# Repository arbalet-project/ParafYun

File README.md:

# Paraf Project

**Paraf** is an opensource digital water curtain.

## Paraf Yún

Paraf Yún is the first version, whose conception started in October, 2018.
Yún's hardware and software resources are designed by and for University students.
Have a look to the [students' logbook](http://talk.arbalet-project.org/t/paraf-yun-en/126) ([lire en français](http://talk.arbalet-project.org/t/paraf-yun-fr/129/)).

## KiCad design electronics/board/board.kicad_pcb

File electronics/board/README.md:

# BOM

Model / Package
IRF7404 / SO-8
ST485 / SO-8
ULN2803A / DW R-PDSO-G18
Crystal TXC HC-495
LMV7805 / DGK S-PDSO-G8

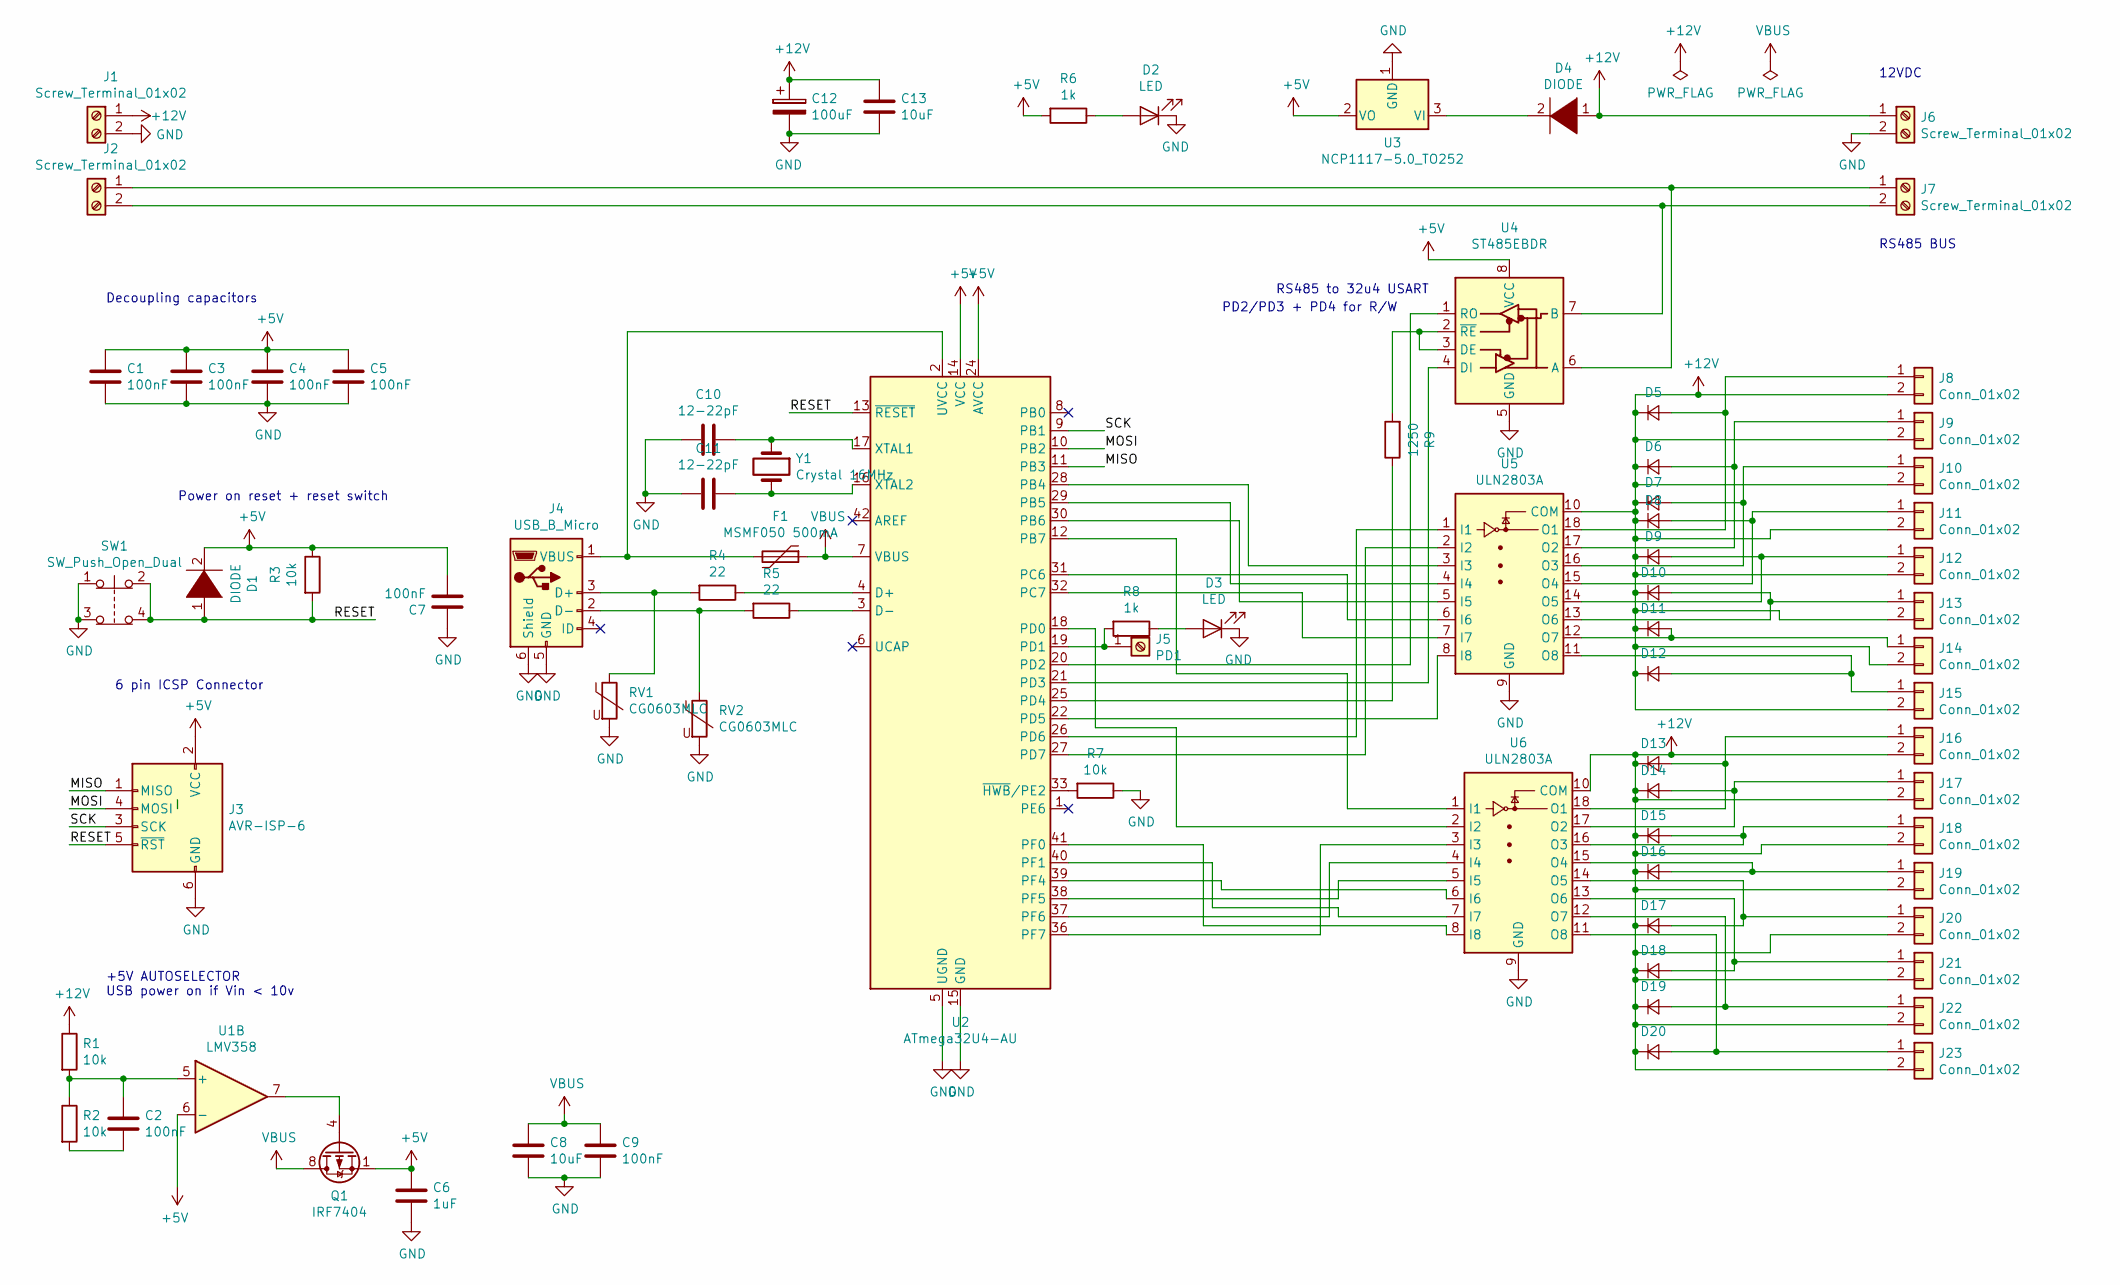
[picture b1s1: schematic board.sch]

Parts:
C1, C2, C3, C4, C5, C7, C9: 100nF; C_0805_2012Metric_Pad1.15x1.40mm_HandSolder
C6: 1uF; C_0805_2012Metric_Pad1.15x1.40mm_HandSolder
C8, C13: 10uF; C_0805_2012Metric_Pad1.15x1.40mm_HandSolder
C10, C11: 12-22pF; C_0805_2012Metric_Pad1.15x1.40mm_HandSolder
C12: 100uF; CP_Elec_6.3x5.2
D1: DIODE; D_0805_2012Metric_Pad1.15x1.40mm_HandSolder
D2, D3: LED; LED_0805_2012Metric
D4: DIODE; D_1206_3216Metric_Pad1.42x1.75mm_HandSolder
D5, D6, D7, D8, D9, D10, D11, D12, D13, D14, D15, D16, D17, D18, D19, D20: D; D_0805_2012Metric_Pad1.15x1.40mm_HandSolder
F1: MSMF050 500mA; Fuse_1812_4532Metric
J1, J2, J6, J7: Screw_Terminal_01x02; TerminalBlock_4Ucon_1x02_P3.50mm_Vertical
J3: AVR-ISP-6; PinHeader_2x03_P2.54mm_Vertical_SMD
J4: USB_B_Micro; USB_Micro-B_Molex_47346-0001
J5: PD1; TestPoint_Keystone_5005-5009_Compact
J8, J9, J10, J11, J12, J13, J14, J15, J16, J17, J18, J19, J20, J21, J22, J23: Conn_01x02; JST_XH_S2B-XH-A_1x02_P2.50mm_Horizontal
Q1: IRF7404; SOIC-8_3.9x4.9mm_P1.27mm
R1, R2, R3, R7: 10k; R_0805_2012Metric_Pad1.15x1.40mm_HandSolder
R4, R5: 22; R_0805_2012Metric_Pad1.15x1.40mm_HandSolder
R6, R8: 1k; R_0805_2012Metric_Pad1.15x1.40mm_HandSolder
R9: 1250; R_0805_2012Metric_Pad1.15x1.40mm_HandSolder
RV1, RV2: CG0603MLC; R_0805_2012Metric_Pad1.15x1.40mm_HandSolder
SW1: SW_Push_Open_Dual; SW_SPST_TL3342
U1: LMV358; MSOP-8-1EP_3x3mm_P0.65mm_EP2.54x2.8mm_ThermalVias
U2: ATmega32U4-AU; TQFP-44_10x10mm_P0.8mm
U3: NCP1117-5.0_TO252; TO-252-2
U4: ST485EBDR; SOIC-8_3.9x4.9mm_P1.27mm
U5, U6: ULN2803A; SOP-18_7.0x12.5mm_P1.27mm
Y1: Crystal 16MHz; Crystal_SMD_SeikoEpson_MC405-2Pin_9.6x4.1mm

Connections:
+5V: C1.1, C3.1, C4.1, C5.1, C6.1, C7.2, D1.2 (A), J3.2 (VCC), Q1.1 (S), Q1.2 (S), Q1.3 (S), R3.1, R6.2, U1.6 (-), U2.14 (VCC), U2.24 (AVCC), U2.34 (VCC), U2.44 (AVCC), U3.2 (VO), U4.8 (VCC)
+12V: C12.1, C13.1, D4.1 (K), D5.1 (K), D6.1 (K), D7.1 (K), D8.1 (K), D9.1 (K), D10.1 (K), D11.1 (K), D12.1 (K), D13.1 (K), D14.1 (K), D15.1 (K), D16.1 (K), D17.1 (K), D18.1 (K), D19.1 (K), D20.1 (K), J1.1, J6.1, J8.2, J9.2, J10.2, J11.2, J12.2, J13.2, J14.2, J15.2, J16.2, J17.2, J18.2, J19.2, J20.2, J21.2, J22.2, J23.2, R1.1, U5.10 (COM), U6.10 (COM)
/MISO: J3.1 (MISO), U2.11 (PB3)
/MOSI: J3.4 (MOSI), U2.10 (PB2)
/RESET: D1.1 (K), J3.5 (~RST), R3.2, SW1.2, SW1.4, U2.13 (~RESET)
/SCK: J3.3 (SCK), U2.9 (PB1)
GND: C1.2, C3.2, C4.2, C5.2, C6.2, C7.1, C8.2, C9.2, C10.1, C11.1, C12.2, C13.2, D2.1 (K), D3.1 (K), J1.2, J3.6 (GND), J4.5 (GND), J4.6 (Shield), J6.2, R7.1, RV1.2, RV2.2, SW1.1, SW1.3, U2.5 (UGND), U2.15 (GND), U2.23 (GND), U2.35 (GND), U2.43 (GND), U3.1 (GND), U4.5 (GND), U5.9 (GND), U6.9 (GND)
unnamed: C2.1, R1.2, R2.1, U1.5 (+)
unnamed: C2.2, R2.2
unnamed: C10.2, U2.17 (XTAL1), Y1.1
unnamed: C11.2, U2.16 (XTAL2), Y1.2
unnamed: D2.2 (A), R6.1
unnamed: D3.2 (A), R8.1
unnamed: D4.2 (A), U3.3 (VI)
unnamed: D5.2 (A), J8.1, U5.18 (O1)
unnamed: D6.2 (A), J9.1, U5.17 (O2)
unnamed: D7.2 (A), J10.1, U5.16 (O3)
unnamed: D8.2 (A), J11.1, U5.15 (O4)
unnamed: D9.2 (A), J12.1, U5.14 (O5)
unnamed: D10.2 (A), J13.1, U5.13 (O6)
unnamed: D11.2 (A), J14.1, U5.12 (O7)
unnamed: D12.2 (A), J15.1, U5.11 (O8)
unnamed: D13.2 (A), J16.1, U6.18 (O1)
unnamed: D14.2 (A), J17.1, U6.17 (O2)
unnamed: D15.2 (A), J18.1, U6.16 (O3)
unnamed: D16.2 (A), J19.1, U6.15 (O4)
unnamed: D17.2 (A), J20.1, U6.14 (O5)
unnamed: D18.2 (A), J21.1, U6.13 (O6)
unnamed: D19.2 (A), J22.1, U6.12 (O7)
unnamed: D20.2 (A), J23.1, U6.11 (O8)
unnamed: F1.2, J4.1 (VBUS), U2.2 (UVCC)
unnamed: J2.1, J7.1, U4.6 (A)
unnamed: J2.2, J7.2, U4.7 (B)
unnamed: J4.2 (D-), R5.2, RV2.1
unnamed: J4.3 (D+), R4.2, RV1.1
unnamed: J5.1, R8.2, U2.19 (PD1)
unnamed: Q1.4 (G), U1.7
unnamed: R4.1, U2.4 (D+)
unnamed: R5.1, U2.3 (D-)
unnamed: R7.2, U2.33 (~HWB~/PE2)
unnamed: R9.1, U2.25 (PD4)
unnamed: R9.2, U4.2 (~RE), U4.3 (DE)
unnamed: U2.12 (PB7), U6.1 (I1)
unnamed: U2.18 (PD0), U6.2 (I2)
unnamed: U2.20 (PD2), U4.1 (RO)
unnamed: U2.21 (PD3), U4.4 (DI)
unnamed: U2.22 (PD5), U5.8 (I8)
unnamed: U2.26 (PD6), U5.1 (I1)
unnamed: U2.27 (PD7), U5.2 (I2)
unnamed: U2.28 (PB4), U5.3 (I3)
unnamed: U2.29 (PB5), U5.4 (I4)
unnamed: U2.30 (PB6), U5.5 (I5)
unnamed: U2.31 (PC6), U5.6 (I6)
unnamed: U2.32 (PC7), U5.7 (I7)
unnamed: U2.36 (PF7), U6.3 (I3)
unnamed: U2.37 (PF6), U6.4 (I4)
unnamed: U2.38 (PF5), U6.5 (I5)
unnamed: U2.39 (PF4), U6.6 (I6)
unnamed: U2.40 (PF1), U6.7 (I7)
unnamed: U2.41 (PF0), U6.8 (I8)
VBUS: C8.1, C9.1, F1.1, Q1.5 (D), Q1.6 (D), Q1.7 (D), Q1.8 (D), U2.7 (VBUS)

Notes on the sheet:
+5V AUTOSELECTOR USB power on if Vin < 10v
12VDC
RS485 BUS
Power on reset + reset switch
Decoupling capacitors
6 pin ICSP Connector
RS485 to 32u4 USART
PD2/PD3 + PD4 for R/W

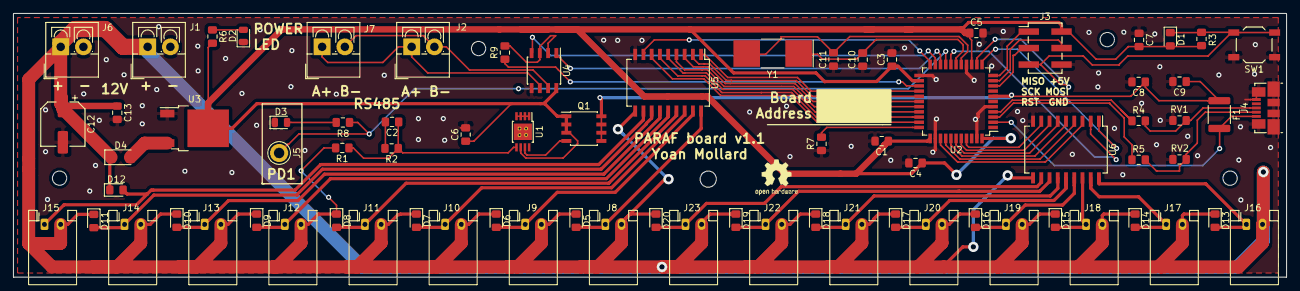
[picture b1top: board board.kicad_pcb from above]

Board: 2 copper layers, 196.2 x 40.6 mm, 77 parts (0 on the bottom side), 61 nets.

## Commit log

2018-11-22 Server django de base. Il n'a rien dans le code pour le moment, on s'entraine encore sur comment fonctionne le serveur. Un repertoire static a été créé pour mettre le code front-end.
2018-11-22 Commit initial du front-end
2018-11-22 Added unterminated PCB
2018-11-24 Deleted + ignored PYC files
2018-11-24 Bugfix style and slider
    + use regular lower case naming
2018-11-29 Suppression de polls. Début implémentation finale du back-end.
2018-11-29 Back-end fonctionnel. Il faut continuer de modifier le HTML avec les balises pour Django.
2018-12-10 Les requêtes GET et GET /sequence fonctionnent. La requête POST ne fonctionne pas pour le moment car le client connecté au serveur n'a pas de token d'authentification. Par conséquent le serveur n'acc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
2018-12-11 Applied migrations
2018-12-13 ajout de la fonction de sauvegarde de la séquence et des appels de fonctions dans index.html
2018-12-13 correction de bugs
2018-12-13 modifications du front-end
2018-12-17 + Bootstrap 3.3.7
2018-12-17 Bugfixes sliders
2018-12-17 Board update
2018-12-17 Missing NC and PRO file update
2018-12-20 Ajout post et sauvegardes
2018-12-20 les paramètres de la séquence se mettent maintenant dans un JSON
2018-12-20 Création du Post en back end non fonctionnelle
2018-12-27 Bugfixes csrf
2019-01-10 Renvoi d'un Json cohérent dans le Get et mise en place du post
2019-01-10 requetes GET et POST depuis le front end fonctionelles (le POST pour sûr le GET pas testé)
2019-01-10 Modification du post
2019-01-10 bug fix
2019-01-12 Board annotation
2019-01-14 Footprints and models
2019-01-15 485 corrections
2019-01-15 Added layout
2019-01-15 Footprint placement v1
2019-01-16 5V regulator bug
2019-01-16 Routing update
2019-01-16 GND + mounting holes
2019-01-16 Edited Silks layers
2019-01-16 Silk update
2019-01-17 added axios
2019-01-17 bug fix du get post
2019-01-20 Transistor fix + LEDs
2019-01-20 Missing board cache
2019-01-20 Final routing and copper zones
2019-01-20 Switching to 0805
2019-01-21 Diode protects only MCU
2019-01-21 Bugfixes R 10k and 12v track
2019-03-03 Board v1.1 (not routed)
2019-03-03 Routed 1.1
2019-03-07 PCB layout
2019-03-07 cut layer + refilled zones
2019-03-07 silk improved
2019-03-09 Improved silk
